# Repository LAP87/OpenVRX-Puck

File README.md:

# OpenVRX-Puck

> Part of the [OpenVRX](https://github.com/LAP87/OpenVRX) family.

A portable analog FPV ground station without a screen: two 5.8 GHz receivers
on the same channel, two video decoders, an FPGA that keeps the cleaner signal
line by line, and HDMI out to goggles, XR glasses or a TV. Battery powered,
two buttons and a small OLED. It stands on the ground when you sit, or hangs
from a lanyard or clip when you stand. SMA connectors for screw-on patch and
omni antennas.

**Status: planned / early design.** The first board, rev A, is a decoder
board (2x TVP5150AM1 to pin headers) that plugs into a Tang Nano 20K running
[OpenVRX-Core](https://github.com/LAP87/OpenVRX-Core)'s `m6_puck_proto`. Its
schematic exists as a script (SKiDL), passes ERC and is checked against the
gateware pin plan and shared RESETB/SPI roles. A KiCad 9 project with the
netlist imported (126 parts, outline, mounting holes, net classes; DRC without
errors, the unconnected pads are the routing still to do) is in
`design/rev_a/kicad/`. Nothing is routed, and no hardware has been tested.

## Why

A display-less puck separates the receiver from the display. Per-line
selection and blending are implemented in Core; real RF improvement and
camera-to-display latency remain unmeasured. The current output is 720p,
so compatibility with a chosen display must be checked before an XR build.

## Specifications (targets, not measured)

| | |
|---|---|
| Receivers | 2x RX5808 (SPI mod), tuned together over SPI; 48 channels |
| Antennas | 2x SMA bulkhead (patch + omni); shield-lid air patch as a later option |
| Decoders | 2x TVP5150AM1 (rev A board) |
| FPGA | Tang Nano 20K (GW2AR-18) for the prototype |
| Output | HDMI 720p (buffered, or genlocked low-latency) |
| RSSI | both receivers to an ADS1115 I2C ADC on the rev A board, read once per field |
| UI | 2 buttons, 0.91" 128x32 OLED, on-screen menu, USB-UART measurement log |
| Power | 2S 21700 Li-ion; USB-C PD in/out via IP2368 (planned) |
| Enclosure | thin tough resin, internal shield can grounded to circuit ground |

## Constraints

- Hobby prototype first, built from modules where possible.
- Receivers and FPGA stay as plug-in modules until the rest works.
- Self-interference matters: the gateware's snow meter and UART log exist to
  measure it (HDMI on/off, channel, shielding).

## Repository

| Path | What |
|---|---|
| `core/` | [OpenVRX-Core](https://github.com/LAP87/OpenVRX-Core) as a git submodule, pinned to a tested version |
| `design/rev_a/` | Decoder board schematic script, generated netlist/BOM/connection list, KiCad project (`kicad/`), layout and lifecycle notes |
| `design/PUCK_2027_KONCEPT.md` | Product concept: outputs, power, enclosure, EMI, antennas (Swedish) |
| `design/REV_A_KONCEPT.md` | Earlier integrated-board concept, now rev B (Swedish) |

## Pinned Core

The `core/` submodule pins Core `ff2efcebdde148515d1f35d460ab64cb03586f0d`, the commit Core's
tag `v0.1-prehw` points to; this repository's tag of the same name is on the commit that pins it.
Together they are the baseline before hardware, described in the hub's
[docs/RELEASE_v0.1-prehw.md](https://github.com/LAP87/OpenVRX/blob/main/docs/RELEASE_v0.1-prehw.md).
On that commit the full Core suite has 772 tests: 769 pass and 3 are strict expected failures
for open findings of the second adversarial review (Core #21-#23), one process per
simulation test. M0, M3, M2a, M4 and M6 are built from it with default options (seed 2 for
M6, 0 for the others), every clock above its 75 MHz requirement after routing, and the
HDMI pairs of M4 and M6 packed as in M0; M6's pack call includes `--mspi_as_gpio` for the
onboard flash ports. LUT4 counts, clocks and bitstream hashes are in the release note.

Vertical interpolation remains off, the transmitter defaults to DVI, and the
varying LOW line stays after vsync. M6 with both `VINTERP=1` and `HDMI=1` places since
Core c822606 (the mixer FIFOs moved to block RAM). SDRAM pin timing and HDMI
compatibility remain unmeasured on hardware.

```sh
git clone --recurse-submodules https://github.com/LAP87/OpenVRX-Puck
pip install skidl==2.3.0 pytest==9.1.1
python -m pytest -q tests
python design/rev_a/dekoderkort.py     # ERC, design rules, Core pin and signal-role checks
```

The schematic was generated with AI assistance from the datasheets
and reviewed by the project owner and one external model. The plan is to
redraw it in KiCad by hand before layout, which is also its most useful review.

## License

[CERN-OHL-S-2.0](https://ohwr.org/cern_ohl_s_v2.txt), see [LICENSE](LICENSE).

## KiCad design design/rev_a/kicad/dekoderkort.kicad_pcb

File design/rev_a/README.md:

# Rev A — dekoderkort (2× TVP5150AM1)

Status 2026-10-05: **schema som kod, ERC rent, ingen layout, inget hårdvaruprov.** RESETB ligger på J6-18; genererade utdata och Core-submodulen ska följa samma version. Det här är ett konstruktionsunderlag, inte ett tillverkningsgodkännande.

Varför ett dekoderkort och inte hela goggle-elektroniken: se [navets vägval](https://github.com/LAP87/OpenVRX/blob/main/research/ALTERNATIVA_VAGAR_2026-10-02.md). Dekoderdelen är gemensam för vägar med egen mixning. Kopplingen är avsedd för Tang Nano 20K rev 3923 och andra FPGA-kort via korta ledningar; faktisk funktion och signalintegritet är ännu inte provade.

## Vad kortet gör

```
mottagare A ─ CVBS ─┐ ESD → 2×37,4 Ω (75 Ω term., ÷2) → [AAF-plats] → 0,1 µF → TVP5150AM1 #A ─ BT.656 + SCLK ─┐
mottagare B ─ CVBS ─┘                    (samma)                              TVP5150AM1 #B ─ BT.656 + SCLK ─┤
                                         egen 14,31818 MHz-kristall per dekoder                              ├─ 2× 1×20 stiftlist
5 V (från Tang J5-1 via lödbygel, eller egen kontakt) → 3,3 V LDO → 2× 1,8 V LDO (digital / analog via ferrit) ┘   = Tang Nano 20K J6 / J5
```

- **Stiftlisterna är numrerade som Tang Nano 20K:s J6 och J5.** Stift n till stift n ger signalplanen för M3/M4/M6 (`../../core/gateware/boards/`). Skriptet kontrollerar hela dekoderkartan för varje topp, både stiftnummer och RESETB/SPI-funktion; kortrevision och kabeldragning kontrolleras på bänken.
- Mottagarkontakterna (JST-PH 4-pol: +5 V, GND, CVBS, RSSI; till 2026-10-13 3-pol utan RSSI) matar varsin mottagare via en PTC-säkring med minst 0,75 A *hold*-ström (inte trip). Mottagaren drar ca 0,45 A; en 0,5 A-del klarar enligt Bourns MF-NSMF-kurvan bara ca 0,44 A vid 40 °C och 0,35 A vid 60 °C. Serien och 1206-footprinten är ännu inte kontrollerade.
- I2C: gemensam SCL och separat SDA per dekoder är standardkopplingen: JP1 öppen, båda YOUT7/I2CSEL-strappade till 7-bitarsadress 5Ch (8-bitars skrivadress B8h). De nuvarande M3/M4/M6-bitströmmarna använder `SPLIT_SDA=1` och adresserna 5Ch/5Ch. Att stänga JP1 och strappa B till 5Dh (BAh) stöds inte av dessa bitströmmar; det kräver en separat verifierad tvåadresskonfiguration. Adressbytet ensamt räcker inte.
- **Två ESD-klampar per videoingång** (2026-10-13, Puck #3, ägarens beslut A): ESD9B5.0 vid kontakten som förut, och en ESD9B3.3 efter spänningsdelaren vid dekoderns ingångsnät. Den första klampar vid 12,5–15 V för en 8 kV-puls och delaren halverar, så 6–7 V skulle nå kopplingskondensatorn framför en ingång som tål 2,0 V; den andra tar större delen av energin intill dekodern och halverar toppen igen. Det är inte ett fullständigt skydd: TI:s referenskoppling har ingen klamp här, och resten av pulsen tas av AAF-spolen och dekoderns egna dioder. Omonterad (DNP) går den att jämföra på bänken. ~15 pF vid ett 18-ohmsnät påverkar inte videon.
- RESETB från FPGA:n på J6-18 (Tang-stift 18, som också driver kortets lysdiod 3). Lysdiodens 510 Ω mot 3,3 V innebär att RESETB inte hålls låg före FPGA-konfiguration. TVP-utgångarna är odefinierade tills en resetpuls har givits; nuvarande `tvp_ctrl` väntar 20 ms efter konfiguration, håller RESETB låg i 2 ms och lämnar sedan YOUT avstängda tills register 03h skrivs. Se [Core bring-up, avsnitt 5](../../core/gateware/BRINGUP.md#5-delade-stift-på-tang-nano-20k-rev-3923). Tidigare låg RESETB på J6-10 (stift 25), som ligger i HDMI-banken och är skärmens CEC-ledning (Puck issue #1, Core issue #6).
- RSSI från båda mottagarna till en I2C-ADC på dekoder A:s buss, se "RSSI" nedan.
- Testpunkter: CVBS, RSSI, SCLK och de separata synksignalerna (HSYNC/VSYNC/AVID/FID) per dekoder. Dessutom en jordpad vid vardera stiftlist (TP för GND), nära SCLK-stiftet: en mätprobs jordfjäder eller en kort returtråd där ger liten slinga när 27 MHz-klockan mäts.

## RSSI (tillagt 2026-10-13)

Ägarens beslut 2026-10-13 (navets `docs/BESLUT_2026-10-12.md`, punkt 7): en I2C-ADC på rev A. Tang Nano 20K har ingen ADC, och mixern ser i dag fading först när raderna redan är förstörda. Lärdomarna från rx5808-pro-diversity och FENIX står i navets `research/RX5808_PRO_DIVERSITY_2026-10-13.md`.

```
mottagare A, stift 4 ─┬─ 100 kΩ ─ GND        ┌─ AIN0
                      └─ 10 kΩ ─┬────────────┤
                                 0,1 µF      │  ADS1115 (48h) ── SDA_A, SCL (dekoder A:s buss)
mottagare B, stift 4  (samma) ───────────────┴─ AIN1         AIN2/AIN3 till GND, ALERT/RDY öppen
```

- **Krets:** TI ADS1115IDGSR, 16 bitar, 8–860 SPS, VSSOP-10. Den har fyra ingångar; två används. Stiftning, adress och regler för oanvända stift är kontrollerade mot TI SBAS444E (tabell 4-1, tabell 7-2, avsnitt 9.1.4). Databladet ingår inte i repot.
- **Adress 48h** (ADDR till GND). Bussarna har redan dekodrarna på 5Ch eller 5Dh och OLED:en på 3Ch; ADS1115 kan bara ha 48h–4Bh, så ingen strappning krockar. `rssi_checks` i skriptet kontrollerar det.
- **Matning 3,3 V**, som I2C-pull-upparna, med 0,1 µF vid VDD. Ingångarna tål GND − 0,3 V till VDD + 0,3 V.
- **Filtret:** 100 kΩ pull-down vid kontakten ger 0 V utan mottagare (samma värde som FENIX). 10 kΩ och 0,1 µF ger τ = 1 ms: en fading syns inom samma fält, och radfrekvensens rippel (15,7 kHz) dämpas cirka 40 dB. 10 kΩ begränsar också strömmen in i ADC:ns skyddsdioder till under 0,2 mA om RSSI skulle nå 5 V.
- **Fälttakt räcker nu.** Core läser båda kanalerna en gång per fält (50–60 Hz; uppgift 14 i navets arbetsplan). Det räcker för tidig varning till mixern, kanalscanning och loggen. Vid 475 SPS tar två omvandlingar cirka 4 ms av fältets 17–20 ms.
- **Radtakt är rev B.** RSSI för varje rad, som FENIX använder för antennbyte, kräver minst 15–30 kSPS. Det betyder en SPI-ADC eller en FPGA med inbyggd ADC, inte en I2C-krets.
- **Kalibrering:** inga två RX5808 har samma RSSI-omfång. Core sparar min och max per mottagare (uppgift 14 och 15). Testpunkten på RSSI-nätet gör det möjligt att jämföra ADC-värdet med en multimeter.
- **Inte kontrollerat:** RSSI-stiftets spänningsomfång och utgångsimpedans hos de mottagare som ska användas, och om de har ett RSSI-stift som går att nå. Mät det innan ADC:ns mätområde väljs i Core.

## Filer

| Fil | Innehåll |
|---|---|
| `dekoderkort.py` | Schemat (SKiDL). Kör: `.venv/bin/python design/rev_a/dekoderkort.py` |
| `out/dekoderkort.net` | KiCad-netlista (importera i Pcbnew när footprints är kontrollerade) |
| `out/dekoderkort_bom.csv` | Stycklista grupperad per värde/footprint |
| `out/dekoderkort_kopplingar.md` | Läsbar lista: varje dels stift → nät |
| `review/` | Underlag för extern granskning (databladsutdrag + uppdrag) |
| `LAYOUT.md` | Underlag för layouten: mått och sandwich mot Tang Nano 20K, lagerstack, placering per block, ledningsregler, jord, värme, mekanik (2026-10-13) |

## Kontroller som körs varje gång

1. **SKiDL ERC**: inga fel och inga varningar (medvetet oanslutna stift är markerade NC).
2. **Databladsregler** (`design_checks`): RSSI-ADC:n på dekoder A:s buss med en ledig adress, 3,3 V och filter plus pull-down på varje RSSI-ingång (`rssi_checks`, med negativa kontroller i testet: fel SDA, 5 V, ombytta ingångar, adresskrock, ingen pull-down, ingen filterkondensator); alla 32 TVP-stift anslutna, rätt matning per stift (IO_DVDD 3,3 V, DVDD 1,8 V digital, CH_AVDD/PLL_AVDD 1,8 V bakom egna ferriter), ingen 3,3 V/5 V-del på XTAL1-näten, exakt en pull-up per I2C-linje.
3. **Mot gateware**: varje dekodersignal på stiftlisterna jämförs separat med FPGA-stiften i `m3_probe.cst`, `m4_dual_mix.cst` och `m6_puck_proto.cst`. Saknade, dubbla eller kolliderande relevanta stiftbegränsningar avvisas. Core kräver dessutom entydig direkt RESETB/SPI-tilldelning till LED3/4/5 i M3/M4/M6. Negativa kontroller lämnar RESETB oansluten, byter D0/D1 på M3/M6, flyttar båda klockor och alla I2C-signaler på varje topp, tar bort/dubblerar stiftbegränsningar och tar bort kontraktskontrollen. Alla avvisas. En äldre Core utan kontraktet kan inte godkännas genom enbart stiftnummer.

Vid regel- eller ERC-fel avslutas scriptet före netlista/BOM/kopplingsrapport skrivs över. Del- och nättaggar är stabila mellan körningar; netlistans genereringsdatum kan ändras. Regression: `.venv/bin/python -m pytest -q tests` från Pucks rot.

Utdata: 126 delar, 87 anslutna nät (124 före den andra ESD-klampen 2026-10-13; 114 och 83 före RSSI). Två körningar gav samma innehåll när genereringsdatumet normaliserades. Netlisteloggen har separata varningar om saknade KiCad-footprintbibliotek och den tomma rot-tagg som KiCad kräver; inga slumpmässiga del-/nättaggar genereras. ERC-resultatet verifierar därför inte footprints eller layout.

## Granskning

- Extern granskning via A0 (DeepSeek V4 Pro) gick inte: **A0-kvoten var slut** (`quota_exhausted` i ledgern 2026-10-02). Efter projektägarens godkännande kördes granskningen i stället med **Nemotron 3 Ultra (gratis, OpenCode Zen)**. Körningen gjordes i en isolerad mapp med bara de tre filerna i `review/`, i läsläge (agent `plan`). Resultat: `review/review_nemotron3ultra_opencode.md`.
  - **Inga fel.** Alla 32 stift, matningar, kristallkrets, ingångskedja och styrstift fick OK.
  - Varningar, alla redan öppna punkter: antialiasfiltret (nu en platshållare, 0 Ω + ej monterad C; TI: "highly recommended"), ESD-diodens modell och kristallens lastkondensatorer.
  - Not om stift 27: 10 k pull-down gäller så länge INTREQ är avstängt. Vår `tvp_ctrl` skriver 03h = 0Dh (bit 5 = 0, avstängt), så det stämmer. Skulle INTREQ användas som aktivt låg interrupt krävs pull-up i stället (figur 6-1 not I).
  - Modellens svar är obekräftad text. Varje punkt ovan är kontrollerad mot databladsutdraget av mig.
- Egen genomgång mot SLES209E tabell 2-1, avsnitt 3.16/3.18 och figur 6-1: inga avvikelser. Saker att bevaka vid komponentval:
  - **XTAL1 tål max 2,3 V** (absoluta maxvärden), VIH = 0,7 × PLL_AVDD. Därför en kristall per dekoder. Idén i `../REV_A_KONCEPT.md` med en gemensam oscillator fungerar bara med en **1,8 V**-oscillator, aldrig med en vanlig på 3,3 V.
  - ~~AMS1117 kräver ESR~~ → bytt till LDO:er som är stabila med keramiska kondensatorer (se Komponentval).
  - Kristallens lastkondensatorer: CL1 = CL2 = 2·CL − C_stray (TI 3.16) → 33 pF för vald kristall (CL 20 pF).
  - TVP:ns utgångar driver bara 2 mA (SCLK 4 mA). Kabeln till FPGA-kortet ska därför vara kort, och 33 Ω-serieresistorerna sitter vid TVP:n.

## Komponentval (2026-10-02)

| Funktion | Del | LCSC | Varför |
|---|---|---|---|
| 5 V → 3,3 V | Diodes **AP7361C-33E-13**, SOT-223 | C500795 | Stabil med keramiska kondensatorer (≥ 2,2 µF). 0,29 W vid ~170 mA ger +32 °C (θJA 110 °C/W). **Stiftning 1 = IN, 2 = GND, 3 = OUT**, inte AMS1117-ordningen. |
| 3,3 V → 1,8 V ×2 (digital / analog) | Diodes **AP2112K-1.8TRG1**, SOT-23-5 | C176944 | 1 µF keramisk räcker. 0,12 W styck. Stiftning 1 = VIN, 2 = GND, 3 = EN (till VIN), 5 = VOUT. |
| ESD på videoingångarna | onsemi **ESD9B5.0ST5G**, SOD-923, bidirektionell | C111566 | AC-kopplade mottagarutgångar går under 0 V. ~15 pF ger en pol vid ~280 MHz, ingen påverkan på video. |
| Antialiasfilter | **0,47 µH** (0603, SRF > 100 MHz) i serie + **1 nF C0G** mot jord | att välja | Se nedan. |
| Kristall | YXC **X32251431818MSB4SI**, 14,31818 MHz, CL 20 pF, ±10 ppm (±20 ppm över −40…85 °C), SMD3225 | C34748 | TVP kräver ±50 ppm. |
| Lastkondensatorer | **33 pF C0G** ×2 per kristall | basic | CL1 = CL2 = 2·20 pF − ~5 pF strökapacitans ≈ 35 pF. Trimmas efter uppmätt SCLK om det behövs. |
| RSSI-ADC | TI **ADS1115IDGSR**, VSSOP-10 | — | Två av fyra ingångar, 48h, 3,3 V. Se "RSSI". |
| TVP5150AM1 | TVP5150AM1**I**PBSR (industriklass, −40…85 °C) | — | Bytt från handelsklassen PBSR (0…70 °C) i Puck #3: kortet sitter i ett slutet hus bredvid två mottagare och ett FPGA-kort. C10013 gäller handelsklassen och är inte kontrollerat för I-klassen; leverantör och lagerstatus okontrollerade. |

Alternativ som noterats: LCSC har en 14,31818 MHz-oscillator för **1,8 V** (C16851, CTS, ±25 ppm). Den gör en gemensam klocka till båda XTAL1 säker, om det någon gång behövs.

Datablad för LDO:erna: se tillverkarnas webbplatser (Diodes Inc.); de ingår inte i repot.

### Antialiasfiltret, räknat

Mottagarens utgång (75 Ω) och spänningsdelaren 2 × 37,4 Ω ger filtret en källa på ≈ 28 Ω. En LC på 0,47 µH / 1 nF (andra ordningen) ger f0 7,3 MHz och Q 0,77:

| Frekvens | Dämpning |
|---|---|
| 4,2 MHz (lumabandbredd) | 0,0 dB |
| 6 MHz | −1,0 dB |
| 13,5 MHz (halva samplingstakten 27 MHz) | −10,6 dB |
| 27 MHz | −22,6 dB |

Färgbärvågen (3,58/4,43 MHz) påverkas inte. En mottagare med nästan 0 Ω utgång ger högst +2,1 dB överslängning, mot 0,1 dB med 75 Ω. Ett 0 Ω-motstånd på spolens plats kopplar förbi filtret.

## Ingångsdelaren, alternativ för starka videonivåer

2 × 37,4 Ω (figur 6-1) är kvar. Om en mottagare ger för hög videonivå kan 47 Ω i serie och 27 Ω mot jord användas (TI SLEU044) på samma 0402-platser. Summan är 74 Ω, en fortfarande rimlig 75 Ω-avslutning, men delningen går från 0,50 till 0,36 (−8,8 dB mot −6 dB). Källimpedansen in i antialiasfiltret sjunker från ca 28 till ca 22 Ω, så filtret bör räknas om om det monteras. Inget av detta är provat.

## PLL-matningen

Varje dekoders PLL_AVDD ligger bakom en egen ferrit och hade bara 0,1 µF efter den. Pärlan är induktiv långt under sina 100 MHz och en liten keramikkondensator har nästan ingen ESR, så de bildar en svagt dämpad LC. Därför finns nu även 4,7 µF efter pärlan (4–10 µF duger), med 0,1 µF kvar vid stiftet. Värdet är en bedömning, inte uppmätt eller simulerat.

## Livscykel

Grundkontrollen är från 2026-10-04. Industrivarianten TVP5150AM1IPBSR kontrollerades hos TI 2026-10-06 och är Active: [LIFECYCLE.md](LIFECYCLE.md). Leverantör och småvolymstillgång för den är fortfarande okontrollerade; hela BOM:en ska kontrolleras igen före kortbeställning.

## Kontroller (tillägg)

- Regulatorernas in- och utgångar kontrolleras mot rätt matningsnät. Provat med en avsiktligt felvänd 3,3 V-regulator, och kontrollen slår larm. (Kontrollen gäller näten; att stiftnumren i deldefinitionen följer databladet är kontrollerat manuellt mot DS37274 och AP2112-databladet.)

## Öppna punkter

- PTC:n är bytt till minst 0,75 A hold (Puck #2); serie, footprint och verkligt strömdrag mot temperatur återstår att kontrollera. ESD-kedja behöver granskas före layout (Puck #2–#3).
- LCSC-nummer för kristall och spole, PTC-säkring och kontaktvarianter.
- Layout: underlaget står i [LAYOUT.md](LAYOUT.md). Måtten för att sätta kortet direkt på Tang Nano 20K (båda stiftlisterna) är inte kontrollerade mot Sipeeds måttritning, och en sandwich kräver kontakter för OLED och RX5808-SPI som schemat saknar (LAYOUT.md, avsnitt 7).
- KiCad är inte installerat på datorn; netlistan har inte importerats ännu.

## KiCad-projekt (tillagt 2026-10-14)

`kicad/dekoderkort.kicad_pro` och `kicad/dekoderkort.kicad_pcb` görs av `kicad/make_board.py` ur netlistan, med KiCad 9:s egen python (`pcbnew`), inte projektets venv:

```
python3 design/rev_a/kicad/make_board.py
kicad-cli pcb drc --severity-error -o drc.rpt design/rev_a/kicad/dekoderkort.kicad_pcb
```

Vad som ligger i kortfilen: konturen 66 × 58 mm och Tang Nano 20K:s kontur som kommentar, de fyra M2-hålen 3,5 mm från hörnen, hylslisterna J2 och J3 där Tang-kortets J6 och J5 landar när det sitter centrerat (radavstånd 20,32 mm; inte kontrollerat mot Sipeeds måttritning, och stift 1-änden är antagen, se `LAYOUT.md` avsnitt 1), alla övriga 120 delar i rader utanför konturen i blockordningen från `LAYOUT.md` avsnitt 3 med blocknamnet intill, alla 86 nät på sina lödytor, fyra kopparlager, tillverkningsgränserna 0,15/0,15 mm och via 0,6/0,3, och nätklasserna 27M (0,35 mm, avstånd 0,7), CVBS (0,15 mm, avstånd 1,2), POWER5 (0,8 mm) och POWER (0,5 mm) som mönster i projektfilen. Ingen ledning är dragen; DRC med KiCad 9.0.9 ger 0 fel och 245 oanslutna lödytor, vilket är de ledningar som ska dras. Placeringen innanför konturen och routningen görs för hand i Pcbnew efter `LAYOUT.md`. Filerna är genererade; ändra skriptet, inte filerna, tills layouten börjar. `tests/test_kicad_project.py` kontrollerar kortfilen mot netlistan (delar, footprints, nät) och projektfilens nätklasser utan `pcbnew`, med en negativ kontroll.

KiCad 9.0.9 finns i WSL (Ubuntu) sedan 2026-10-14 (ägarens beslut 8); Pcbnew går att öppna därifrån med WSLg (`pcbnew design/rev_a/kicad/dekoderkort.kicad_pcb`), eller installeras på Windows.

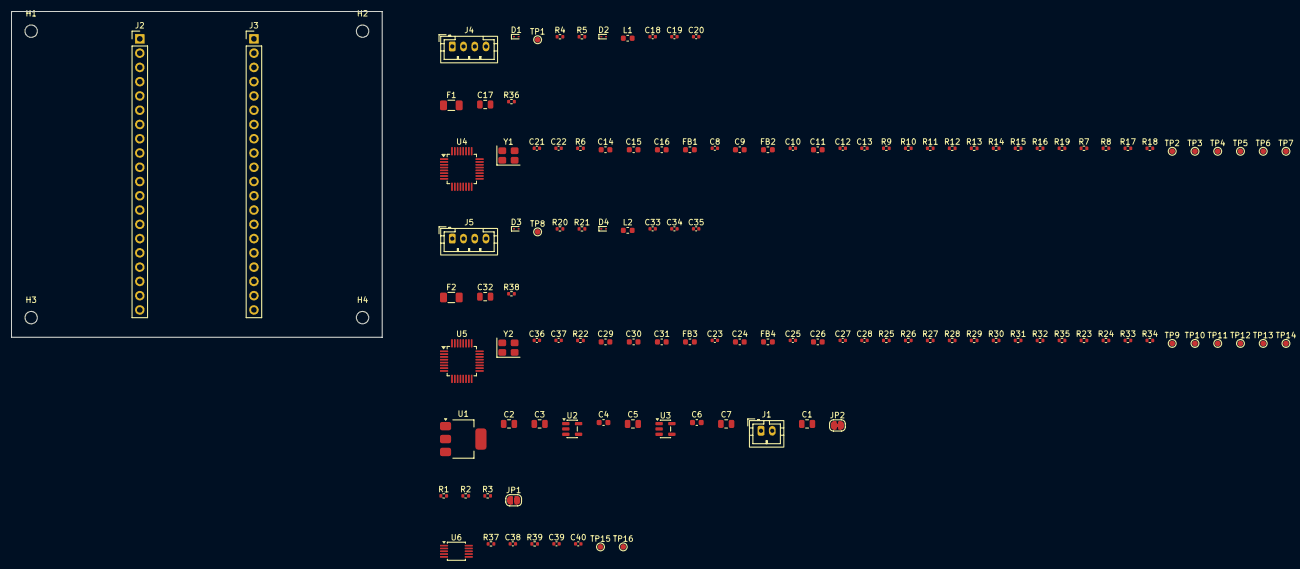
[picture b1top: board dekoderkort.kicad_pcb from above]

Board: 4 copper layers, 66.0 x 58.0 mm, 126 parts (0 on the bottom side), 86 nets, no tracks yet.

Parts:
C1: 22u; C_0805_2012Metric
C2, C3, C5, C7, C17, C32: 10u; C_0805_2012Metric
C4, C6, C9, C14, C15, C16, C24, C29, C30, C31: 1u; C_0603_1608Metric
C8, C10, C12, C13, C19, C20, C23, C25, C27, C28, C34, C35, C38, C39, C40: 0.1u; C_0402_1005Metric
C11, C26: 4.7u; C_0603_1608Metric
C18, C33: 1n C0G; C_0402_1005Metric
C21, C22, C36, C37: 33p C0G; C_0402_1005Metric
D1, D3: ESD9B5.0ST5G; D_SOD-923
D2, D4: ESD9B3.3ST5G; D_SOD-923
F1, F2: 0.75A hold PTC; Fuse_1206_3216Metric
FB1, FB2, FB3, FB4: BLM18KG601SN1D; L_0603_1608Metric
H1, H2, H3, H4: MountingHole_M2; MountingHole_2.2mm_M2
J1: PWR_IN; JST_PH_B2B-PH-K_1x02_P2.00mm_Vertical
J2, J3: PinHeader_1x20; PinHeader_1x20_P2.54mm_Vertical
J4: VIDEO_IN_A; JST_PH_B4B-PH-K_1x04_P2.00mm_Vertical
J5: VIDEO_IN_B; JST_PH_B4B-PH-K_1x04_P2.00mm_Vertical
JP1: SolderJumper_2_Open; SolderJumper-2_P1.3mm_Open_RoundedPad1.0x1.5mm
JP2: SolderJumper_2_Bridged; SolderJumper-2_P1.3mm_Bridged_RoundedPad1.0x1.5mm
L1, L2: 0.47uH; L_0603_1608Metric
R1, R2, R3: 4.7k; R_0402_1005Metric
R4, R5, R20, R21: 37.4; R_0402_1005Metric
R6, R22, R36, R38: 100k; R_0402_1005Metric
R7, R8, R17, R23, R24, R33, R37, R39: 10k; R_0402_1005Metric
R9, R10, R11, R12, R13, R14, R15, R16, R19, R25, R26, R27, R28, R29, R30, R31, R32, R35: 33; R_0402_1005Metric
R18, R34: DNP 10k; R_0402_1005Metric
TP1, TP2, TP3, TP4, TP5, TP6, TP8, TP9, TP10, TP11, TP12, TP13, TP15, TP16: TestPoint; TestPoint_Pad_D1.0mm
TP7, TP14: TestPoint_GND; TestPoint_Pad_D1.0mm
U1: AP7361C-33E-13; SOT-223-3_TabPin2
U2, U3: AP2112K-1.8TRG1; SOT-23-5
U4, U5: TVP5150AM1IPBSR; TQFP-32_5x5mm_P0.5mm
U6: ADS1115IDGSR; VSSOP-10_3x3mm_P0.5mm
Y1, Y2: X32251431818MSB4SI; Crystal_SMD_3225-4Pin_3.2x2.5mm

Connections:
+1V8_A: C7.1, FB1.1, FB2.1, FB3.1, FB4.1, U3.5
+1V8_D: C5.1, C12.1, C27.1, U2.5, U4.20, U5.20
+3V3: C3.1, C4.1, C6.1, C13.1, C28.1, C40.1, R1.2, R2.2, R3.2, R7.2, R18.2, R23.2, R34.2, U1.3, U2.1, U2.3, U3.1, U3.3, U4.10, U5.10, U6.8
+5V: C1.1, C2.1, F1.1, F2.1, J1.1, JP2.2, U1.1
+5V_RX_A: C17.1, F1.2, J4.1
+5V_RX_B: C32.1, F2.2, J5.1
+5V_TANG: J3.1, JP2.1
AIP1A_A: C19.2, U4.1
AIP1A_B: C34.2, U5.1
AIP1B_A: C20.1, U4.2
AIP1B_B: C35.1, U5.2
AVDD_A: C8.1, C9.1, FB1.2, U4.32
AVDD_B: C23.1, C24.1, FB3.2, U5.32
AVID_A: TP5.1, U4.26
AVID_B: TP12.1, U5.26
A_SCLK_U: R19.1, U4.9
A_YOUT0_U: R9.1, U4.18
A_YOUT1_U: R10.1, U4.17
A_YOUT2_U: R11.1, U4.16
A_YOUT3_U: R12.1, U4.15
A_YOUT4_U: R13.1, U4.14
A_YOUT5_U: R14.1, U4.13
A_YOUT6_U: R15.1, U4.12
A_YOUT7_I2CSEL_U: R16.1, R17.1, R18.1, U4.11
B_SCLK_U: R35.1, U5.9
B_YOUT0_U: R25.1, U5.18
B_YOUT1_U: R26.1, U5.17
B_YOUT2_U: R27.1, U5.16
B_YOUT3_U: R28.1, U5.15
B_YOUT4_U: R29.1, U5.14
B_YOUT5_U: R30.1, U5.13
B_YOUT6_U: R31.1, U5.12
B_YOUT7_I2CSEL_U: R32.1, R33.1, R34.1, U5.11
CVBS_A: D1.1, J4.3, R4.1, TP1.1
CVBS_AAF_A: C18.1, C19.1, L1.2
CVBS_AAF_B: C33.1, C34.1, L2.2
CVBS_B: D3.1, J5.3, R20.1, TP8.1
CVBS_DIV_A: D2.1, L1.1, R4.2, R5.1
CVBS_DIV_B: D4.1, L2.1, R20.2, R21.1
FID_GLCO_A: TP2.1, U4.23
FID_GLCO_B: TP9.1, U5.23
GND: C1.2, C2.2, C3.2, C4.2, C5.2, C6.2, C7.2, C8.2, C9.2, C10.2, C11.2, C12.2, C13.2, C14.2, C15.2, C17.2, C18.2, C20.2, C21.2, C22.2, C23.2, C24.2, C25.2, C26.2, C27.2, C28.2, C29.2, C30.2, C32.2, C33.2, C35.2, C36.2, C37.2, C38.2, C39.2, C40.2, D1.2, D2.2, D3.2, D4.2, J1.2, J2.20, J3.2, J3.15, J4.2, J5.2, R5.2, R8.2, R17.2, R21.2, R24.2, R33.2, R36.2, R38.2, TP7.1, TP14.1, U1.2, U2.2, U3.2, U4.3, U4.7, U4.19, U4.31, U5.3, U5.7, U5.19, U5.31, U6.1, U6.3, U6.6, U6.7, Y1.2, Y1.4, Y2.2, Y2.4
HSYNC_A: TP4.1, U4.25
HSYNC_B: TP11.1, U5.25
I2C_SCL: J2.3, R1.1, U4.21, U5.21, U6.10
I2C_SDA_A: J2.4, JP1.1, R2.1, U4.22, U6.9
I2C_SDA_B: J3.9, JP1.2, R3.1, U5.22
INTREQ_A: R8.1, U4.27
INTREQ_B: R24.1, U5.27
PDN_A: R7.1, U4.28
PDN_B: R23.1, U5.28
PLL_AVDD_A: C10.1, C11.1, FB2.2, U4.4
PLL_AVDD_B: C25.1, C26.1, FB4.2, U5.4
REFM_A: C15.1, C16.2, U4.30
REFM_B: C30.1, C31.2, U5.30
REFP_A: C14.1, C16.1, U4.29
REFP_B: C29.1, C31.1, U5.29
RSSI_A: J4.4, R36.1, R37.1, TP15.1
RSSI_ADC_A: C38.1, R37.2, U6.4
RSSI_ADC_B: C39.1, R39.2, U6.5
RSSI_B: J5.4, R38.1, R39.1, TP16.1
TVPA_D0: J2.8, R9.2
TVPA_D1: J2.9, R10.2
TVPA_D2: J2.11, R11.2
TVPA_D3: J2.12, R12.2
TVPA_D4: J2.13, R13.2
TVPA_D5: J2.14, R14.2
TVPA_D6: J2.1, R15.2
TVPA_D7: J2.2, R16.2
TVPA_SCLK: J2.5, R19.2, TP6.1
TVPB_D0: J3.3, R25.2
TVPB_D1: J3.5, R26.2
TVPB_D2: J3.6, R27.2
TVPB_D3: J3.10, R28.2
TVPB_D4: J3.12, R29.2
TVPB_D5: J3.13, R30.2
TVPB_D6: J3.14, R31.2
TVPB_D7: J3.17, R32.2
TVPB_SCLK: J3.4, R35.2, TP13.1
TVP_RESETB: J2.18, U4.8, U5.8
VSYNC_PALI_A: TP3.1, U4.24
VSYNC_PALI_B: TP10.1, U5.24
XTAL1_A: C21.1, R6.1, U4.5, Y1.1
XTAL1_B: C36.1, R22.1, U5.5, Y2.1
XTAL2_A: C22.1, R6.2, U4.6, Y1.3
XTAL2_B: C37.1, R22.2, U5.6, Y2.3

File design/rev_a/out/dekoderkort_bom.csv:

qty,refs,part,value,footprint,note
1,U6,ADS1115,ADS1115IDGSR,Package_SO:VSSOP-10_3x3mm_P0.5mm,"TI ADS1115IDGSR: RSSI A on AIN0, RSSI B on AIN1, read once per field; 8-860 SPS, conversion time 1/DR. ADDR to GND = 48h (table 7-2). AIN2/AIN3 to GND and ALERT/RDY open (section 9.1.4). VDD 3.3 V like the I2C pull-ups"
15,C8 C10 C12 C13 C19 C20 C23 C25 C27 C28 C34 C35 C38 C39 C40,C,0.1u,Capacitor_SMD:C_0402_1005Metric,
6,C2 C3 C5 C7 C17 C32,C,10u,Capacitor_SMD:C_0805_2012Metric,
2,C18 C33,C,1n C0G,Capacitor_SMD:C_0402_1005Metric,
10,C4 C6 C9 C14 C15 C16 C24 C29 C30 C31,C,1u,Capacitor_SMD:C_0603_1608Metric,
1,C1,C,22u,Capacitor_SMD:C_0805_2012Metric,
4,C21 C22 C36 C37,C,33p C0G,Capacitor_SMD:C_0402_1005Metric,
2,C11 C26,C,4.7u,Capacitor_SMD:C_0603_1608Metric,
1,J2,CONN_1x20,PinHeader_1x20,Connector_PinHeader_2.54mm:PinHeader_1x20_P2.54mm_Vertical,Mirror of Tang Nano 20K J6: connect pin n to J6-n
1,J3,CONN_1x20,PinHeader_1x20,Connector_PinHeader_2.54mm:PinHeader_1x20_P2.54mm_Vertical,Mirror of Tang Nano 20K J5: connect pin n to J5-n
1,D2,ESD,ESD9B3.3ST5G,Diode_SMD:D_SOD-923,"second clamp after the divider (A): bidirectional 3.3 V, same family as D1/D2, onsemi Active 2026-10-13; fit, or leave off to compare"
1,D4,ESD,ESD9B3.3ST5G,Diode_SMD:D_SOD-923,"second clamp after the divider (B): bidirectional 3.3 V, same family as D1/D2, onsemi Active 2026-10-13; fit, or leave off to compare"
2,D1 D3,ESD,ESD9B5.0ST5G,Diode_SMD:D_SOD-923,"LCSC C111566, bidirectional 5 V, ~15 pF (pole ~280 MHz at ~37 ohm: no effect on video); bidirectional because AC-coupled receiver outputs swing below 0 V (fig. 6-1 note G)"
1,F1,F,0.75A hold PTC,Fuse:Fuse_1206_3216Metric,"Resettable fuse for receiver A supply, >= 0.75 A HOLD current (SpeedyBee draws ~0.45 A at 5 V); check that the chosen series is available in 1206, else change footprint"
1,F2,F,0.75A hold PTC,Fuse:Fuse_1206_3216Metric,"Resettable fuse for receiver B supply, >= 0.75 A HOLD current (SpeedyBee draws ~0.45 A at 5 V); check that the chosen series is available in 1206, else change footprint"
4,FB1 FB2 FB3 FB4,FB,BLM18KG601SN1D,Inductor_SMD:L_0603_1608Metric,"ferrite bead 600 ohm @ 100 MHz, >= 200 mA"
1,JP2,JP,SolderJumper_2_Bridged,Jumper:SolderJumper-2_P1.3mm_Bridged_RoundedPad1.0x1.5mm,5 V from Tang Nano 20K J5-1 (closed by default); open when powering from J1
1,JP1,JP,SolderJumper_2_Open,Jumper:SolderJumper-2_P1.3mm_Open_RoundedPad1.0x1.5mm,"Default open: split SDA, both decoders 5Ch. Shared SDA/5Ch+5Dh needs a separately verified two-address firmware configuration; current M3/M4/M6 do not support it."
1,L1,L,0.47uH,Inductor_SMD:L_0603_1608Metric,"AAF inductor (A): 0603, SRF > 100 MHz, DCR < 0.5 ohm; or 0 ohm to bypass"
1,L2,L,0.47uH,Inductor_SMD:L_0603_1608Metric,"AAF inductor (B): 0603, SRF > 100 MHz, DCR < 0.5 ohm; or 0 ohm to bypass"
1,U2,LDO_AP2112K,AP2112K-1.8TRG1,Package_TO_SOT_SMD:SOT-23-5,"LCSC C176944. 3.3 V -> 1.8 V digital (2x DVDD), ~66 mA max (0.12 W)"
1,U3,LDO_AP2112K,AP2112K-1.8TRG1,Package_TO_SOT_SMD:SOT-23-5,"LCSC C176944. 3.3 V -> 1.8 V analog (2x CH_AVDD + PLL_AVDD), ~78 mA max (0.12 W)"
1,U1,LDO_AP7361C,AP7361C-33E-13,Package_TO_SOT_SMD:SOT-223-3_TabPin2,"LCSC C500795. 5 V -> 3.3 V for TVP IO_DVDD, pull-ups and both 1.8 V LDOs (~170 mA: 0.29 W, +32 C at 110 C/W)"
4,H1 H2 H3 H4,MH,MountingHole_M2,MountingHole:MountingHole_2.2mm_M2,
1,J1,PWR_IN,PWR_IN,Connector_JST:JST_PH_B2B-PH-K_1x02_P2.00mm_Vertical,Optional 5 V input if not powered from header J5-1
4,R6 R22 R36 R38,R,100k,Resistor_SMD:R_0402_1005Metric,
8,R7 R8 R17 R23 R24 R33 R37 R39,R,10k,Resistor_SMD:R_0402_1005Metric,
18,R9 R10 R11 R12 R13 R14 R15 R16 R19 R25 R26 R27 R28 R29 R30 R31 R32 R35,R,33,Resistor_SMD:R_0402_1005Metric,
4,R4 R5 R20 R21,R,37.4,Resistor_SMD:R_0402_1005Metric,
3,R1 R2 R3,R,4.7k,Resistor_SMD:R_0402_1005Metric,
2,R18 R34,R,DNP 10k,Resistor_SMD:R_0402_1005Metric,
14,TP1 TP2 TP3 TP4 TP5 TP6 TP8 TP9 TP10 TP11 TP12 TP13 TP15 TP16,TP,TestPoint,TestPoint:TestPoint_Pad_D1.0mm,
1,TP7,TP,TestPoint_GND,TestPoint:TestPoint_Pad_D1.0mm,GND pad next to header J2 (SCLK A): probe ground for the 27 MHz clock
1,TP14,TP,TestPoint_GND,TestPoint:TestPoint_Pad_D1.0mm,GND pad next to header J3 (SCLK B): probe ground for the 27 MHz clock
1,U4,TVP5150AM1PBS,TVP5150AM1IPBSR,Package_QFP:TQFP-32_5x5mm_P0.5mm,"TI TVP5150AM1IPBSR, industrial grade -40..85 C; LCSC C10013 is the commercial-grade code and has NOT been checked for this grade (Other Suppliers, per design/REV_A_KONCEPT.md); decoder A"
1,U5,TVP5150AM1PBS,TVP5150AM1IPBSR,Package_QFP:TQFP-32_5x5mm_P0.5mm,"TI TVP5150AM1IPBSR, industrial grade -40..85 C; LCSC C10013 is the commercial-grade code and has NOT been checked for this grade (Other Suppliers, per design/REV_A_KONCEPT.md); decoder B"
1,J4,VIDEO_IN_A,VIDEO_IN_A,Connector_JST:JST_PH_B4B-PH-K_1x04_P2.00mm_Vertical,"Receiver A: 1 = +5 V out (fused), 2 = GND, 3 = CVBS, 4 = RSSI"
1,J5,VIDEO_IN_B,VIDEO_IN_B,Connector_JST:JST_PH_B4B-PH-K_1x04_P2.00mm_Vertical,"Receiver B: 1 = +5 V out (fused), 2 = GND, 3 = CVBS, 4 = RSSI"
2,Y1 Y2,XTAL,X32251431818MSB4SI,Crystal:Crystal_SMD_3225-4Pin_3.2x2.5mm,"YXC 14.31818 MHz, CL 20 pF, +-10 ppm at 25 C / +-20 ppm over -40..85 C, SMD3225-4P (TVP needs +-50 ppm); LCSC C34748. CL1 = CL2 = 2*CL - Cstray = 40 - ~5 -> 33 pF (section 3.16)"
